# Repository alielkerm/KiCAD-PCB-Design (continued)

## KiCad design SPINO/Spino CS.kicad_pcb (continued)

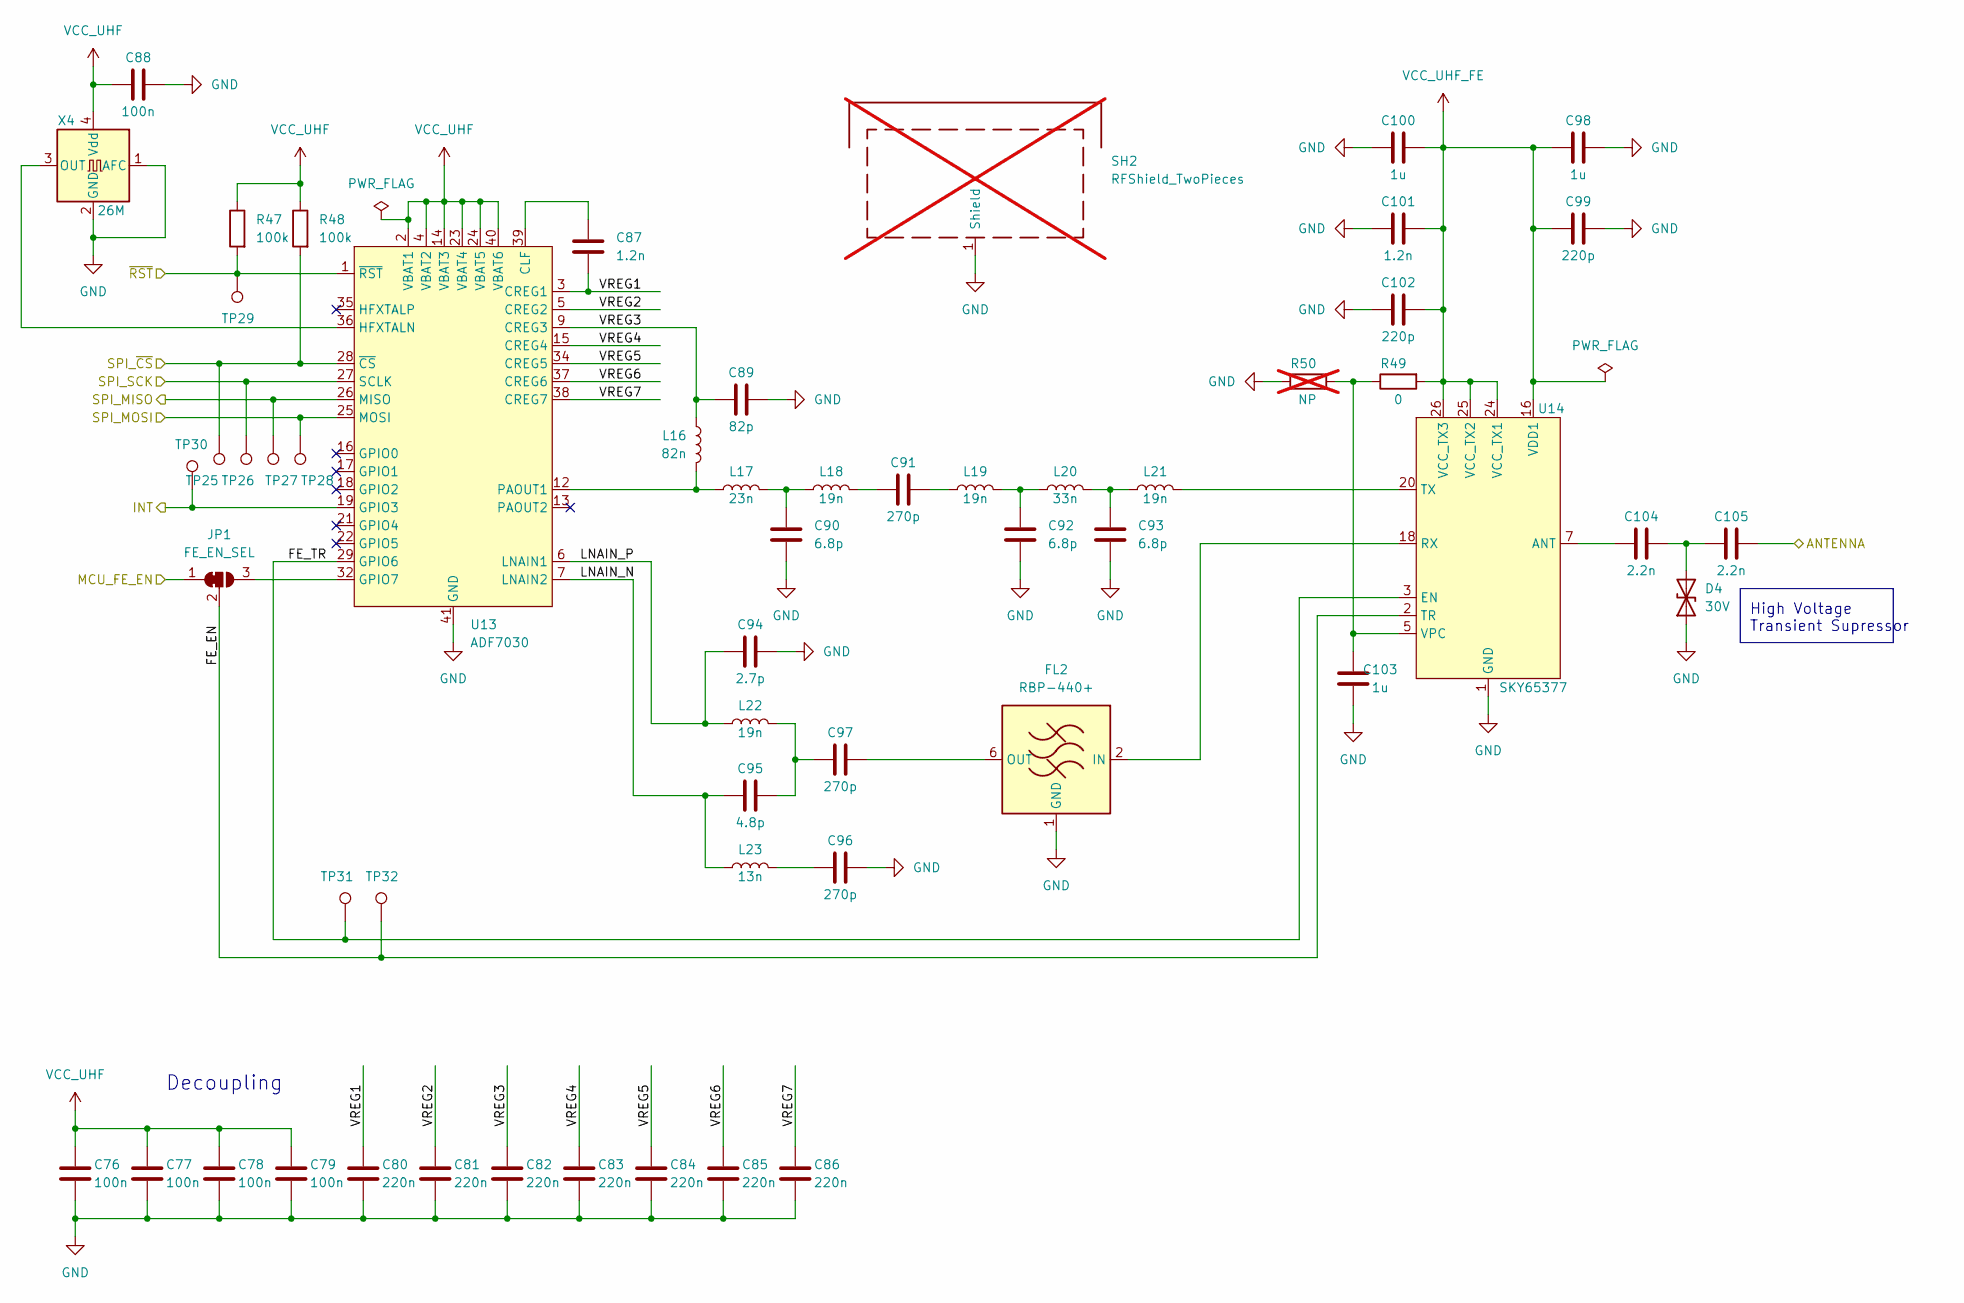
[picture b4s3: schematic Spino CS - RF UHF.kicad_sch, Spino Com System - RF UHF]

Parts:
C76, C77, C78, C79, C88: 100n; C_0402_1005Metric
C80, C81, C82, C83, C84, C85, C86: 220n; C_0402_1005Metric; Tolerance 10%
C87, C101: 1.2n; C_0402_1005Metric; Tolerance 10%
C89: 82p; C_0402_1005Metric; Tolerance 1%
C90, C92, C93: 6.8p; C_0603_1608Metric; Tolerance 0.1p
C91: 270p; C_0603_1608Metric; Tolerance 1%
C94: 2.7p; C_0402_1005Metric; Tolerance 0.05p
C95: 4.8p; C_0402_1005Metric; Tolerance 0.1p
C96, C97: 270p; C_0402_1005Metric; Tolerance 1%
C98, C100, C103: 1u; C_0402_1005Metric
C99, C102: 220p; C_0402_1005Metric; Tolerance 1%
C104, C105: 2.2n; C_0402_1005Metric; Tolerance 10%
D4: 30V; D_0603_1608Metric
FL2: RBP-440+; Mini-Circuits_GP731
JP1: FE_EN_SEL; SolderJumper-3_P0.8mm_Bridged2Bar12_RoundedPad0.6x1.0mm
L16: 82n; L_0603_1608Metric; Tolerance 5%
L17: 23n; L_0402_1005Metric; Tolerance 2%
L18, L19, L21, L22: 19n; L_0402_1005Metric; Tolerance 2%
L20: 33n; L_0402_1005Metric; Tolerance 2%
L23: 13n; L_0402_1005Metric; Tolerance 2%
R47, R48: 100k; R_0402_1005Metric; Tolerance 1%
R49: 0; R_0402_1005Metric
R50: NP; R_0402_1005Metric; not fitted
SH2: RFShield_TwoPieces; Wuerth_3670405_40.5x18.9mm_CustomBottomRightOpening2.2mm; not fitted
TP25: UHF_~{CS}; TestPoint_Pad_D1.0mm
TP26: UHF_SCK; TestPoint_Pad_D1.0mm
TP27: UHF_MISO; TestPoint_Pad_D1.0mm
TP28: UHF_MOSI; TestPoint_Pad_D1.0mm
TP29: UHF_~{RST}; TestPoint_Pad_D1.0mm
TP30: UHF_INT; TestPoint_Pad_D1.0mm
TP31: UHF_FE_TR; TestPoint_Pad_D1.0mm
TP32: UHF_FE_EN; TestPoint_Pad_D1.0mm
U13: ADF7030; LFCSP-40-1EP_6x6mm_P0.5mm_EP4.6x4.6mm
U14: SKY65377; Skyworks_MCM-L-28-1EP_6x6mm_P0.75mm_EP4x4mm
X4: 26M; Oscillator_SMD_TXC_7Z-4Pin_2.0x1.6mm

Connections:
/Processor/UHF_FE_EN: JP1.1 (A); also elsewhere on the board
/Processor/UHF_INT: TP30.1, U13.19 (GPIO3); also elsewhere on the board
/Processor/UHF_SPI_MISO: TP27.1, U13.26 (MISO); also elsewhere on the board
/Processor/UHF_SPI_MOSI: TP28.1, U13.25 (MOSI); also elsewhere on the board
/Processor/UHF_SPI_SCK: TP26.1, U13.27 (SCLK); also elsewhere on the board
/Processor/UHF_SPI_~CS: R48.2, TP25.1, U13.28 (~CS); also elsewhere on the board
/Processor/UHF_~RST: R47.2, TP29.1, U13.1 (~RST); also elsewhere on the board
/RF UHF/ANTENNA: C105.2; also elsewhere on the board
/RF UHF/FE_EN: JP1.2 (C), TP32.1, U14.2 (TR)
/RF UHF/FE_TR: TP31.1, U13.29 (GPIO6), U14.3 (EN)
/RF UHF/LNAIN_N: C95.1, L23.1, U13.7 (LNAIN2)
/RF UHF/LNAIN_P: C94.1, L22.1, U13.6 (LNAIN1)
/RF UHF/VREG1: C80.1, C87.2, U13.3 (CREG1)
/RF UHF/VREG2: C81.1, U13.5 (CREG2)
/RF UHF/VREG3: C82.1, C89.1, L16.1, U13.9 (CREG3)
/RF UHF/VREG4: C83.1, U13.15 (CREG4)
/RF UHF/VREG5: C84.1, U13.34 (CREG5)
/RF UHF/VREG6: C85.1, U13.37 (CREG6)
/RF UHF/VREG7: C86.1, U13.38 (CREG7)
GND: C76.2, C77.2, C78.2, C79.2, C80.2, C81.2, C82.2, C83.2, C84.2, C85.2, C86.2, C88.2, C89.2, C90.2, C92.2, C93.2, C94.2, C96.2, C98.1, C99.1, C100.1, C101.1, C102.1, C103.2, D4.1 (A1), FL2.1 (GND), FL2.3 (GND), FL2.4 (GND), FL2.5 (GND), FL2.7 (GND), FL2.8 (GND), R50.1, SH2.1 (Shield), U13.41 (GND), U14.1 (GND), U14.6 (GND), U14.8 (GND), U14.9 (GND), U14.11 (GND), U14.12 (GND), U14.15 (GND), U14.19 (GND), U14.21 (GND), U14.22 (GND), U14.27 (GND), U14.28 (GND), U14.29 (GND), X4.1 (AFC), X4.2 (GND); also elsewhere on the board
unnamed: C90.1, L17.2, L18.1
unnamed: C91.1, L18.2
unnamed: C91.2, L19.1
unnamed: C92.1, L19.2, L20.1
unnamed: C93.1, L20.2, L21.1
unnamed: C95.2, C97.1, L22.2
unnamed: C96.1, L23.2
unnamed: C104.2, C105.1, D4.2 (A2)
unnamed: FL2.2 (IN), U14.18 (RX)
unnamed: C97.2, FL2.6 (OUT)
unnamed: JP1.3 (B), U13.32 (GPIO7)
unnamed: C87.1, U13.39 (CLF)
unnamed: U13.36 (HFXTALN), X4.3 (OUT)
unnamed: L16.2, L17.1, U13.12 (PAOUT1)
unnamed: C104.1, U14.7 (ANT)
unnamed: L21.2, U14.20 (TX)
unnamed: C103.1, R49.1, R50.2, U14.5 (VPC)
VCC_UHF: C76.1, C77.1, C78.1, C79.1, C88.1, R47.1, R48.1, U13.2 (VBAT1), U13.4 (VBAT2), U13.14 (VBAT3), U13.23 (VBAT4), U13.24 (VBAT5), U13.40 (VBAT6), X4.4 (Vdd); also elsewhere on the board
VCC_UHF_FE: C98.2, C99.2, C100.2, C101.2, C102.2, R49.2, U14.16 (VDD1), U14.24 (VCC_TX1), U14.25 (VCC_TX2), U14.26 (VCC_TX3); also elsewhere on the board

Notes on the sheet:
High Voltage Transient Supressor
Decoupling

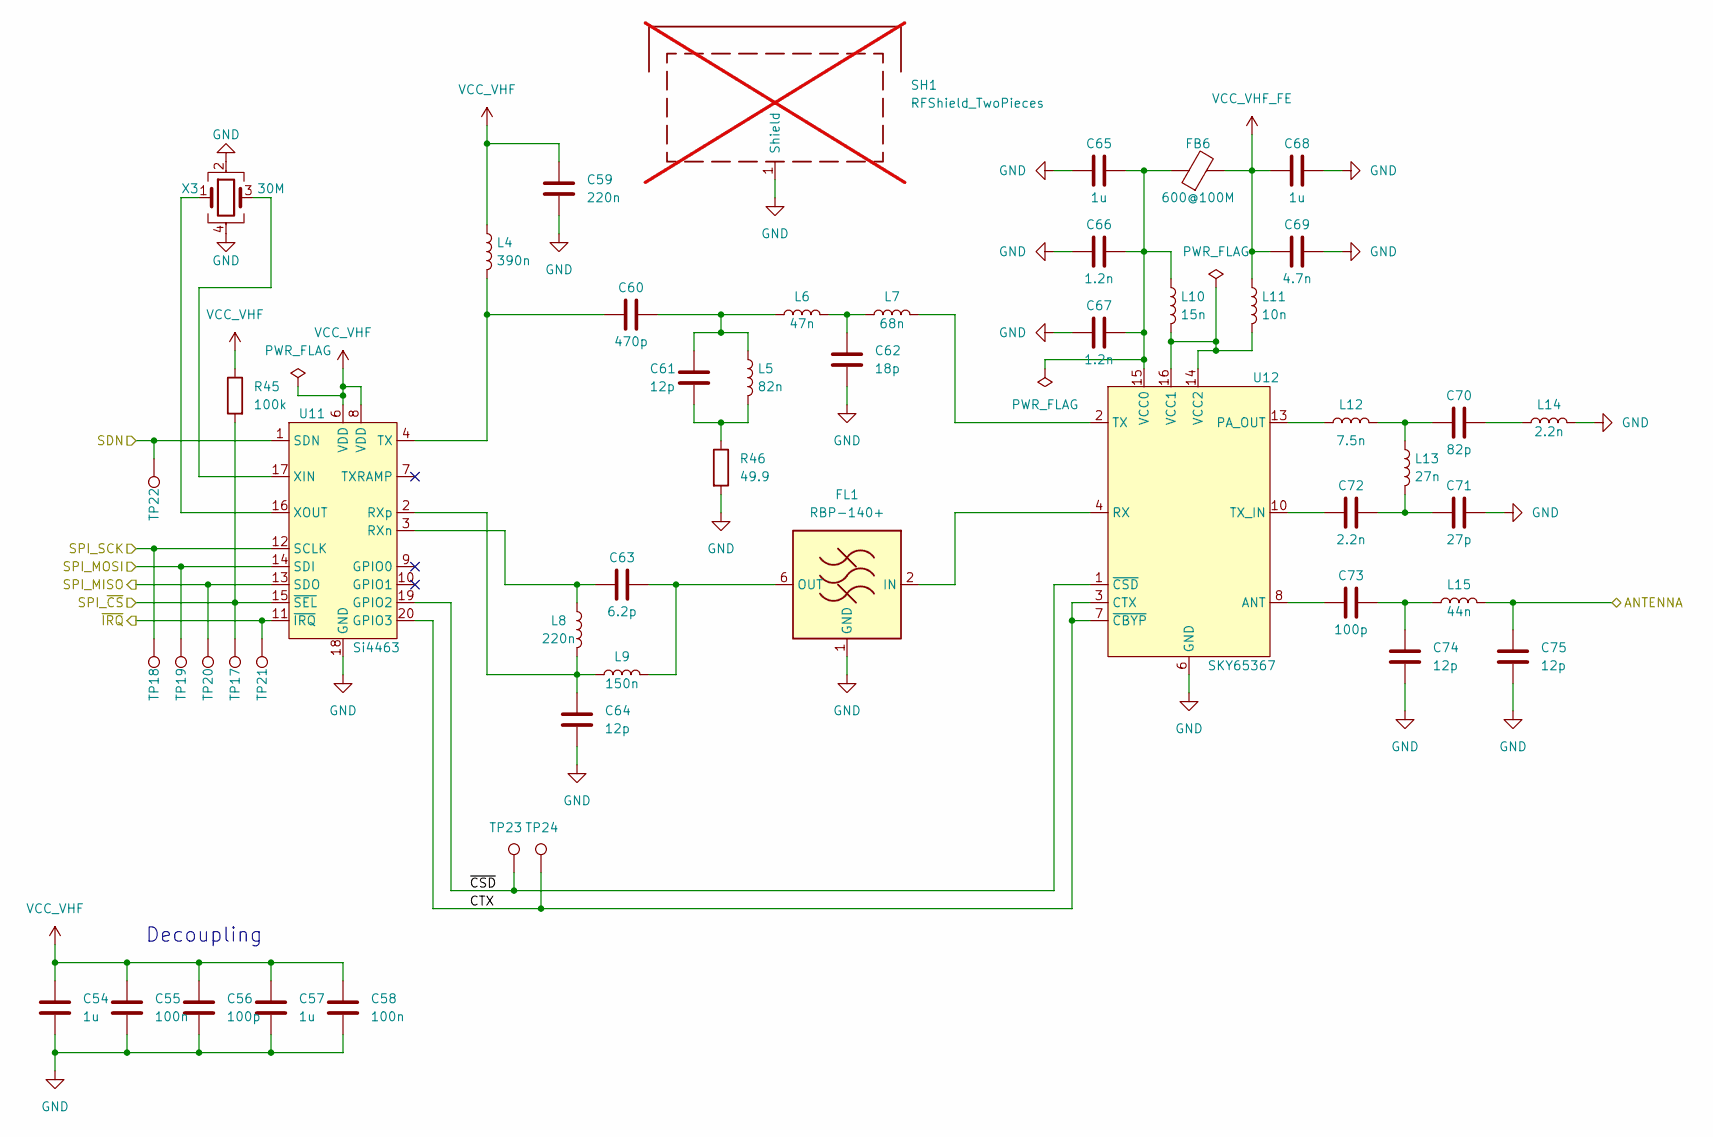
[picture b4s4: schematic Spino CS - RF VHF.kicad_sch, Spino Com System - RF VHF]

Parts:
C54, C57, C65, C68: 1u; C_0402_1005Metric
C55, C58: 100n; C_0402_1005Metric
C56, C73: 100p; C_0402_1005Metric; Tolerance 1%
C59: 220n; C_0402_1005Metric; Tolerance 10%
C60: 470p; C_0402_1005Metric; Tolerance 1%
C61, C64, C74, C75: 12p; C_0603_1608Metric; Tolerance 1%
C62: 18p; C_0603_1608Metric; Tolerance 1%
C63: 6.2p; C_0603_1608Metric; Tolerance 0.1p
C66, C67: 1.2n; C_0402_1005Metric; Tolerance 10%
C69: 4.7n; C_0402_1005Metric; Tolerance 10%
C70: 82p; C_0402_1005Metric; Tolerance 1%
C71: 27p; C_0603_1608Metric; Tolerance 1%
C72: 2.2n; C_0402_1005Metric; Tolerance 10%
FB6: 600@100M; L_0603_1608Metric
FL1: RBP-140+; Mini-Circuits_GP731
L4: 390n; L_0603_1608Metric; Tolerance 5%
L5: 82n; L_0603_1608Metric; Tolerance 5%
L6: 47n; L_0402_1005Metric; Tolerance 2%
L7: 68n; L_0402_1005Metric; Tolerance 2%
L8: 220n; L_0603_1608Metric; Tolerance 5%
L9: 150n; L_0603_1608Metric; Tolerance 5%
L10: 15n; L_0402_1005Metric; Tolerance 5%
L11: 10n; L_0603_1608Metric; Tolerance 5%
L12: 7.5n; L_0603_1608Metric; Tolerance 2%
L13: 27n; L_0603_1608Metric; Tolerance 2%
L14: 2.2n; L_0402_1005Metric; Tolerance 2%
L15: 44n; L_0603_1608Metric; Tolerance 2%
R45: 100k; R_0402_1005Metric; Tolerance 1%
R46: 49.9; R_0603_1608Metric; Tolerance 1%
SH1: RFShield_TwoPieces; Wuerth_3670405_40.5x18.9mm_CustomBottomLeftOpening2.2mm; not fitted
TP17: VHF_~{CS}; TestPoint_Pad_D1.0mm
TP18: VHF_CLK; TestPoint_Pad_D1.0mm
TP19: VHF_MOSI; TestPoint_Pad_D1.0mm
TP20: VHF_MISO; TestPoint_Pad_D1.0mm
TP21: VHF_~{IRQ}; TestPoint_Pad_D1.0mm
TP22: VHF_SDN; TestPoint_Pad_D1.0mm
TP23: VHF_FE_~{CSD}; TestPoint_Pad_D1.0mm
TP24: VHF_FE_CTX; TestPoint_Pad_D1.0mm
U11: Si4463; QFN-20-1EP_4x4mm_P0.5mm_EP2.6x2.6mm
U12: SKY65367; Skyworks_MCM-L-16-1EP_4x4mm_P0.8mm_EP2x2mm
X3: 30M; Crystal_SMD_2016-4Pin_2.0x1.6mm

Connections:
/Processor/VHF_SDN: TP22.1, U11.1 (SDN); also elsewhere on the board
/Processor/VHF_SPI_MISO: TP20.1, U11.13 (SDO); also elsewhere on the board
/Processor/VHF_SPI_MOSI: TP19.1, U11.14 (SDI); also elsewhere on the board
/Processor/VHF_SPI_SCK: TP18.1, U11.12 (SCLK); also elsewhere on the board
/Processor/VHF_SPI_~CS: R45.2, TP17.1, U11.15 (~SEL); also elsewhere on the board
/Processor/VHF_~IRQ: TP21.1, U11.11 (~IRQ); also elsewhere on the board
/RF VHF/ANTENNA: C75.1, L15.2; also elsewhere on the board
/RF VHF/CTX: TP24.1, U11.20 (GPIO3), U12.3 (CTX), U12.7 (~CBYP)
/RF VHF/~CSD: TP23.1, U11.19 (GPIO2), U12.1 (~CSD)
GND: C54.2, C55.2, C56.2, C57.2, C58.2, C59.2, C62.2, C64.2, C65.2, C66.2, C67.2, C68.2, C69.2, C71.2, C74.2, C75.2, FL1.1 (GND), FL1.3 (GND), FL1.4 (GND), FL1.5 (GND), FL1.7 (GND), FL1.8 (GND), L14.2, R46.2, SH1.1 (Shield), U11.18 (GND), U11.21 (GND), U12.6 (GND), U12.9 (GND), U12.11 (GND), U12.12 (GND), U12.17 (GND), X3.2, X3.4; also elsewhere on the board
unnamed: C60.2, C61.1, L5.1, L6.1
unnamed: C61.2, L5.2, R46.1
unnamed: C62.1, L6.2, L7.1
unnamed: C70.1, L12.2, L13.1
unnamed: C70.2, L14.1
unnamed: C71.1, C72.2, L13.2
unnamed: C73.2, C74.1, L15.1
unnamed: FL1.2 (IN), U12.4 (RX)
unnamed: C63.2, FL1.6 (OUT), L9.2
unnamed: C63.1, L8.1, U11.3 (RXn)
unnamed: C64.1, L8.2, L9.1, U11.2 (RXp)
unnamed: C60.1, L4.2, U11.4 (TX)
unnamed: U11.17 (XIN), X3.3
unnamed: U11.16 (XOUT), X3.1
unnamed: C73.1, U12.8 (ANT)
unnamed: L12.1, U12.13 (PA_OUT)
unnamed: L7.2, U12.2 (TX)
unnamed: C72.1, U12.10 (TX_IN)
unnamed: C65.1, C66.1, C67.1, FB6.1, L10.1, U12.15 (VCC0)
VCC_VHF: C54.1, C55.1, C56.1, C57.1, C58.1, C59.1, L4.1, R45.1, U11.6 (VDD), U11.8 (VDD); also elsewhere on the board
VCC_VHF_FE: C68.1, C69.1, FB6.2, L11.1; also elsewhere on the board

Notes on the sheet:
Decoupling

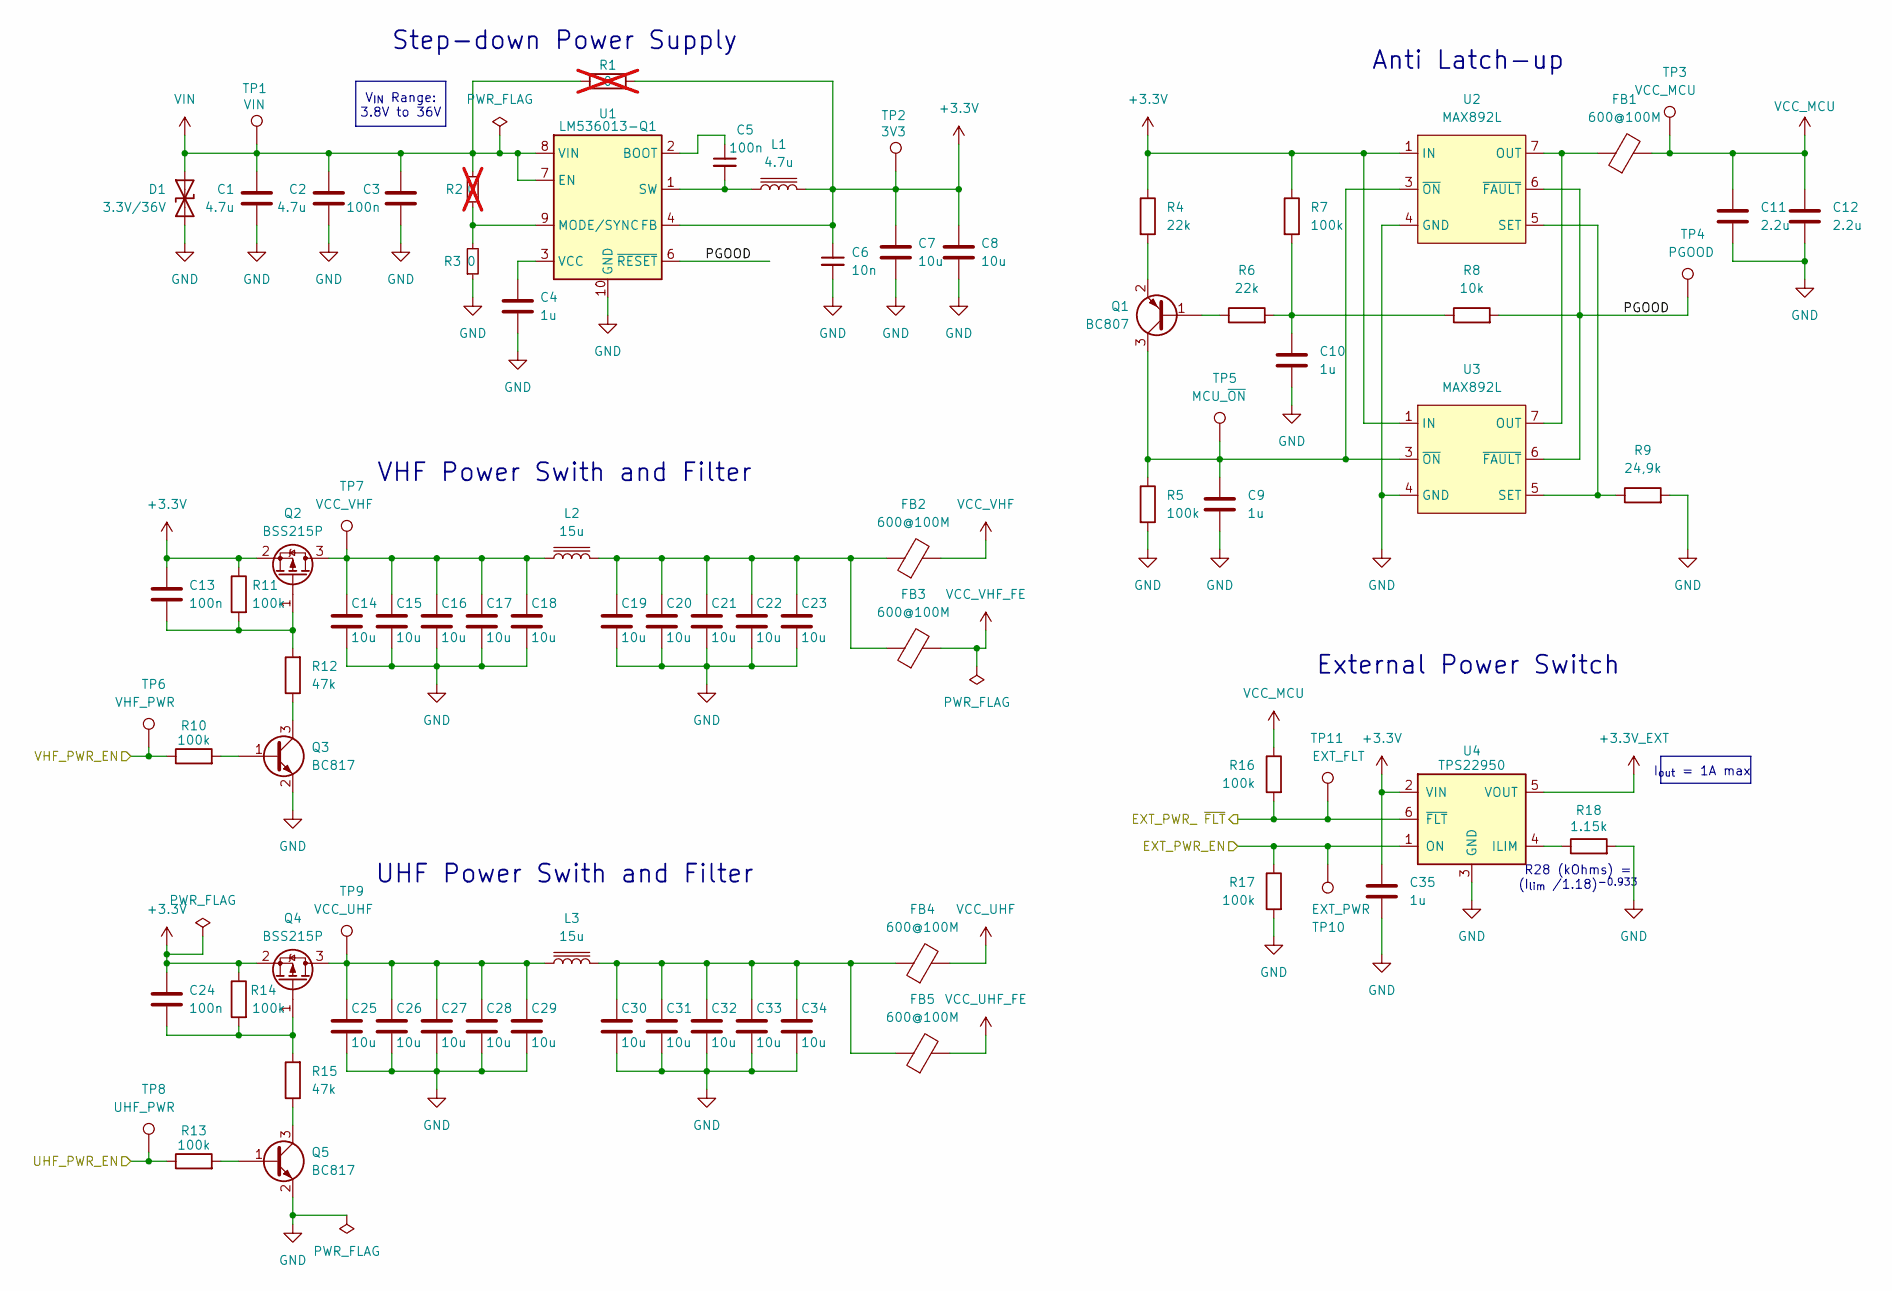
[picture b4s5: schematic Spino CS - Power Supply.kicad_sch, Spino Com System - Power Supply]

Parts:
C1, C2: 4.7u; C_0805_2012Metric; Tolerance 10%
C3: 100n; C_0603_1608Metric
C4: 1u; C_0402_1005Metric
C5, C13, C24: 100n; C_0402_1005Metric
C6: 10n; C_0402_1005Metric
C7, C8, C14, C15, C16, C17, C18, C19, C20, C21, C22, C23, C25, C26, C27, C28, C29, C30, C31, C32, C33, C34: 10u; C_0805_2012Metric; Tolerance 10%
C9, C10, C35: 1u; C_0603_1608Metric; Tolerance 10%
C11, C12: 2.2u; C_0603_1608Metric; Tolerance 10%
D1: 3.3V/36V; D_SOD-123F
FB1, FB2, FB3, FB4, FB5: 600@100M; L_0603_1608Metric
L1: 4.7u; L_Coilcraft_XxL4040
L2, L3: 15u; L_TDK_CLF7045
Q1: BC807; SOT-23
Q2, Q4: BSS215P; SOT-23-3
Q3, Q5: BC817; SOT-23-3
R1: 0; R_0805_2012Metric; not fitted
R2: 0; R_0402_1005Metric; not fitted
R3: 0; R_0402_1005Metric
R4, R6: 22k; R_0402_1005Metric; Tolerance 1%
R5, R7, R10, R11, R13, R14, R16, R17: 100k; R_0402_1005Metric; Tolerance 1%
R8: 10k; R_0402_1005Metric; Tolerance 1%
R9: 24,9k; R_0402_1005Metric; Tolerance 1%
R12, R15: 47k; R_0402_1005Metric; Tolerance 1%
R18: 1.15k; R_0402_1005Metric; Tolerance 1%
TP1: VIN; TestPoint_Pad_D1.0mm
TP2: 3V3; TestPoint_Pad_D1.0mm
TP3: VCC_MCU; TestPoint_Pad_D1.0mm
TP4: PGOOD; TestPoint_Pad_D1.0mm
TP5: MCU_~{ON}; TestPoint_Pad_D1.0mm
TP6: VHF_PWR; TestPoint_Pad_D1.0mm
TP7: VCC_VHF; TestPoint_Pad_D1.0mm
TP8: UHF_PWR; TestPoint_Pad_D1.0mm
TP9: VCC_UHF; TestPoint_Pad_D1.0mm
TP10: EXT_PWR; TestPoint_Pad_D1.0mm
TP11: EXT_FLT; TestPoint_Pad_D1.0mm
U1: LM536013-Q1; Texas_S-PVSON-N10
U2, U3: MAX892L; MSOP-8_3x3mm_P0.65mm
U4: TPS22950; SOT-23-6

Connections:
+3.3V: C6.1, C7.1, C8.1, C13.1, C24.1, C35.1, L1.2, Q2.2 (S), Q4.2 (S), R1.2, R4.1, R7.1, R11.1, R14.1, TP2.1, U1.4 (FB), U2.1 (IN), U2.2 (IN), U3.1 (IN), U3.2 (IN), U4.2 (VIN)
+3.3V_EXT: U4.5 (VOUT); also elsewhere on the board
/Power Supply/EXT_PWR_ ~FLT: R16.2, TP11.1, U4.6 (~FLT); also elsewhere on the board
/Power Supply/EXT_PWR_EN: R17.1, TP10.1, U4.1 (ON); also elsewhere on the board
/Power Supply/PGOOD: R8.2, TP4.1, U1.6 (~RESET), U2.6 (~FAULT), U3.6 (~FAULT)
/Power Supply/UHF_PWR_EN: R13.1, TP8.1; also elsewhere on the board
/Power Supply/VHF_PWR_EN: R10.1, TP6.1; also elsewhere on the board
GND: C1.2, C2.2, C3.2, C4.2, C6.2, C7.2, C8.2, C9.2, C10.2, C11.2, C12.2, C14.2, C15.2, C16.2, C17.2, C18.2, C19.2, C20.2, C21.2, C22.2, C23.2, C25.2, C26.2, C27.2, C28.2, C29.2, C30.2, C31.2, C32.2, C33.2, C34.2, C35.2, D1.2 (A2), Q3.2 (E), Q5.2 (E), R3.1, R5.2, R9.2, R17.2, R18.2, U1.5 (AGND), U1.10 (GND), U1.11 (PAD), U2.4 (GND), U3.4 (GND), U4.3 (GND); also elsewhere on the board
unnamed: C10.1, R6.2, R7.2, R8.1
unnamed: C19.1, C20.1, C21.1, C22.1, C23.1, FB2.1, FB3.1, L2.2
unnamed: C30.1, C31.1, C32.1, C33.1, C34.1, FB4.1, FB5.1, L3.2
unnamed: FB1.1, U2.7 (OUT), U2.8 (OUT), U3.7 (OUT), U3.8 (OUT)
unnamed: Q1.1 (B), R6.1
unnamed: C9.1, Q1.3 (C), R5.1, TP5.1, U2.3 (~ON), U3.3 (~ON)
unnamed: Q1.2 (E), R4.2
unnamed: C14.1, C15.1, C16.1, C17.1, C18.1, L2.1, Q2.3 (D), TP7.1
unnamed: C13.2, Q2.1 (G), R11.2, R12.2
unnamed: Q3.1 (B), R10.2
unnamed: Q3.3 (C), R12.1
unnamed: C25.1, C26.1, C27.1, C28.1, C29.1, L3.1, Q4.3 (D), TP9.1
unnamed: C24.2, Q4.1 (G), R14.2, R15.2
unnamed: Q5.1 (B), R13.2
unnamed: Q5.3 (C), R15.1
unnamed: C5.1, U1.2 (BOOT)
unnamed: R2.1, R3.2, U1.9 (MODE/SYNC)
unnamed: C5.2, L1.1, U1.1 (SW)
unnamed: C4.1, U1.3 (VCC)
unnamed: R9.1, U2.5 (SET), U3.5 (SET)
unnamed: R18.1, U4.4 (ILIM)
VCC_MCU: C11.1, C12.1, FB1.2, R16.1, TP3.1; also elsewhere on the board
VCC_UHF: FB4.2; also elsewhere on the board
VCC_UHF_FE: FB5.2; also elsewhere on the board
VCC_VHF: FB2.2; also elsewhere on the board
VCC_VHF_FE: FB3.2; also elsewhere on the board
VIN: C1.1, C2.1, C3.1, D1.1 (A1), R1.1, R2.2, TP1.1, U1.7 (EN), U1.8 (VIN); also elsewhere on the board

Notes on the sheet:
I_{out} = 1A max
V_{IN} Range: 3.8V to 36V
R28 (kOhms) = (I_{lim} /1.18)^{-0.933}
External Power Switch
Anti Latch-up
Step-down Power Supply
VHF Power Swith and Filter
UHF Power Swith and Filter

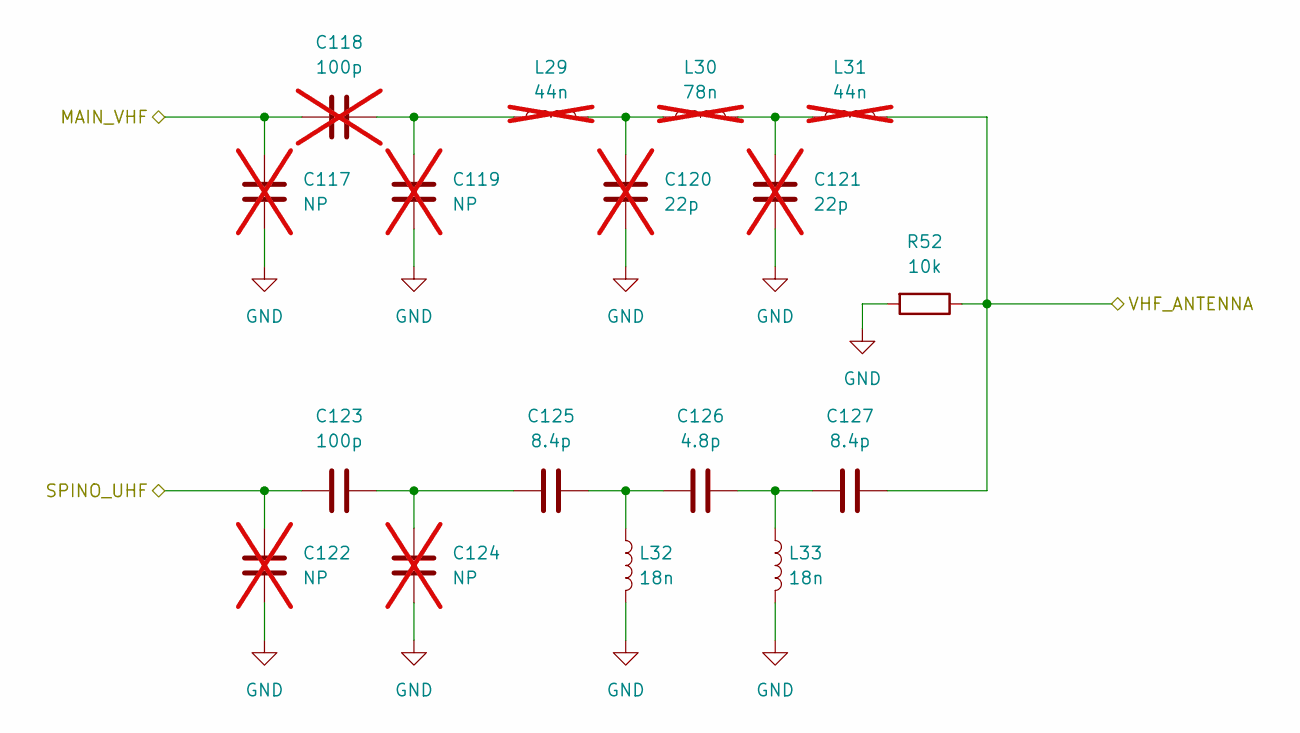
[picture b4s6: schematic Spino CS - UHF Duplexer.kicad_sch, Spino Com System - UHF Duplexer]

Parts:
C117, C119, C122, C124: NP; C_0603_1608Metric; not fitted
C118: 100p; C_0402_1005Metric; Tolerance 1%; not fitted
C120, C121: 22p; C_0603_1608Metric; Tolerance 1%; not fitted
C123: 100p; C_0402_1005Metric; Tolerance 1%
C125, C127: 8.4p; C_0402_1005Metric; Tolerance 0.1p
C126: 4.8p; C_0402_1005Metric; Tolerance 0.1p
L29, L31: 44n; L_0603_1608Metric; Tolerance 2%; not fitted
L30: 78n; L_0603_1608Metric; Tolerance 2%; not fitted
L32, L33: 18n; L_0603_1608Metric; Tolerance 2%
R52: 10k; R_0603_1608Metric; Tolerance 1%

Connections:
/RF UHF/ANTENNA: C122.1, C123.1; also elsewhere on the board
/UHF Duplexer/MAIN_VHF: C117.1, C118.1; also elsewhere on the board
/UHF Duplexer/VHF_ANTENNA: C127.2, L31.2, R52.1; also elsewhere on the board
GND: C117.2, C119.2, C120.2, C121.2, C122.2, C124.2, L32.2, L33.2, R52.2; also elsewhere on the board
unnamed: C118.2, C119.1, L29.1
unnamed: C120.1, L29.2, L30.1
unnamed: C121.1, L30.2, L31.1
unnamed: C123.2, C124.1, C125.1
unnamed: C125.2, C126.1, L32.1
unnamed: C126.2, C127.1, L33.1

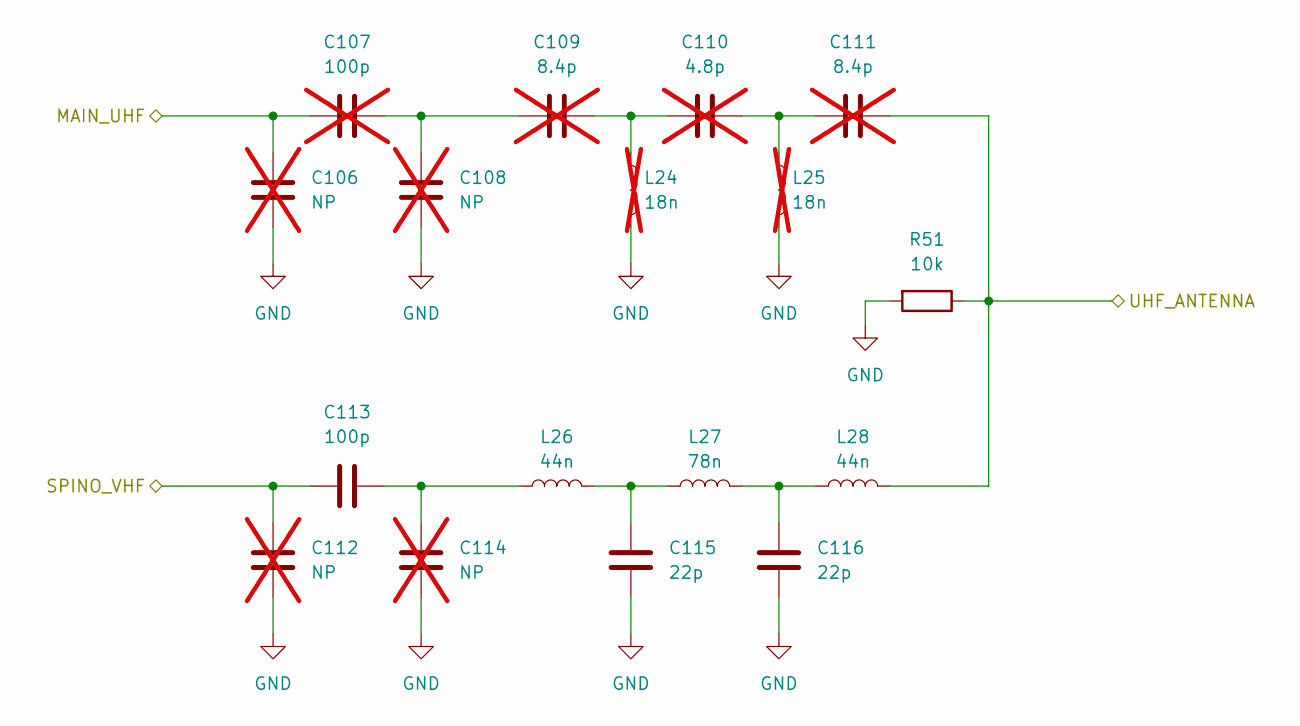
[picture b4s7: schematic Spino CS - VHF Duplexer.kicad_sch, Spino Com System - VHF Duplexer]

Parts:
C106, C108, C112, C114: NP; C_0603_1608Metric; not fitted
C107: 100p; C_0402_1005Metric; Tolerance 1%; not fitted
C109, C111: 8.4p; C_0402_1005Metric; Tolerance 0.1p; not fitted
C110: 4.8p; C_0402_1005Metric; Tolerance 0.1p; not fitted
C113: 100p; C_0402_1005Metric; Tolerance 1%
C115, C116: 22p; C_0603_1608Metric; Tolerance 1%
L24, L25: 18n; L_0603_1608Metric; Tolerance 2%; not fitted
L26, L28: 44n; L_0603_1608Metric; Tolerance 2%
L27: 78n; L_0603_1608Metric; Tolerance 2%
R51: 10k; R_0603_1608Metric; Tolerance 1%

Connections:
/RF VHF/ANTENNA: C112.1, C113.1; also elsewhere on the board
/VHF Duplexer/MAIN_UHF: C106.1, C107.1; also elsewhere on the board
/VHF Duplexer/UHF_ANTENNA: C111.2, L28.2, R51.1; also elsewhere on the board
GND: C106.2, C108.2, C112.2, C114.2, C115.2, C116.2, L24.2, L25.2, R51.2; also elsewhere on the board
unnamed: C107.2, C108.1, C109.1
unnamed: C109.2, C110.1, L24.1
unnamed: C110.2, C111.1, L25.1
unnamed: C113.2, C114.1, L26.1
unnamed: C115.1, L26.2, L27.1
unnamed: C116.1, L27.2, L28.1

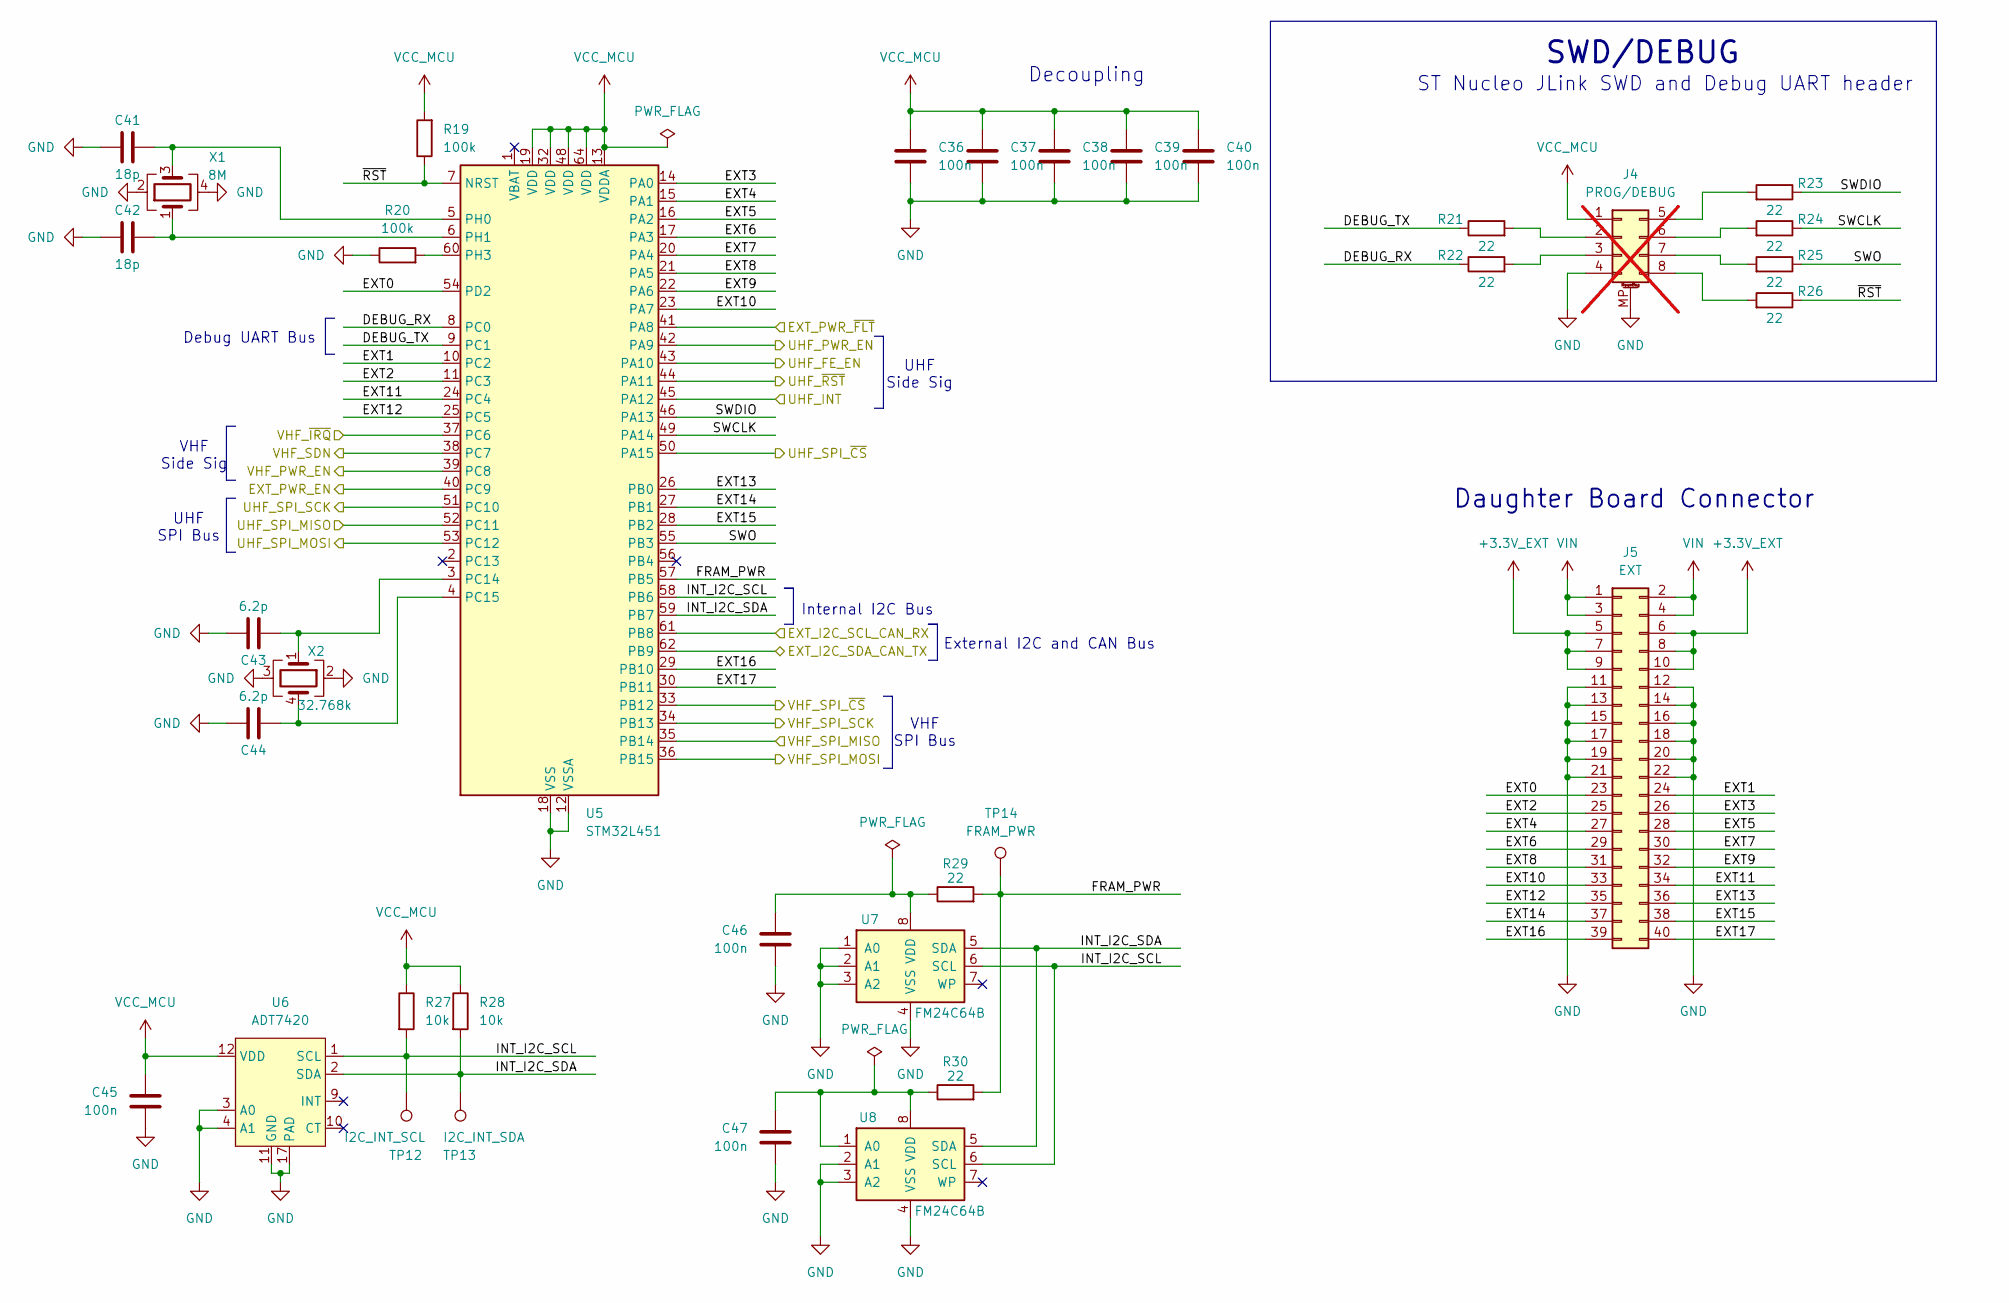
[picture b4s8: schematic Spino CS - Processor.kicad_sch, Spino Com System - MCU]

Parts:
C36, C37, C38, C39, C40, C45, C46, C47: 100n; C_0402_1005Metric
C41, C42: 18p; C_0402_1005Metric; Tolerance 1%
C43, C44: 6.2p; C_0402_1005Metric; Tolerance 0.1p
J4: PROG/DEBUG; Harwin_LTek-Male_2x04_P2.00mm_Horizontal_StrainRelief; not fitted
J5: EXT; Samtec_LSEM-120-xx.x-x-DV-A-N_2x20_P0.80mm_Vertical
R19, R20: 100k; R_0402_1005Metric; Tolerance 1%
R21, R22, R23, R24, R25, R26, R29, R30: 22; R_0402_1005Metric; Tolerance 1%
R27, R28: 10k; R_0402_1005Metric; Tolerance 1%
TP12: I2C_INT_SCL; TestPoint_Pad_D1.0mm
TP13: I2C_INT_SDA; TestPoint_Pad_D1.0mm
TP14: FRAM_PWR; TestPoint_Pad_D1.0mm
U5: STM32L451; LQFP-64_10x10mm_P0.5mm
U6: ADT7420; LFCSP-16-1EP_4x4mm_P0.65mm_EP2.6x2.6mm
U7, U8: FM24C64B; SOIC-8_3.9x4.9mm_P1.27mm
X1: 8M; Crystal_SMD_Abracon_ABM8AIG-4Pin_3.2x2.5mm
X2: 32.768k; Crystal_SMD_Abracon_ABS25-4Pin_8.0x3.8mm

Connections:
+3.3V_EXT: J5.5, J5.6, J5.7, J5.8, J5.9, J5.10; also elsewhere on the board
/Digital Serial/EXT_I2C_SCL_CAN_RX: U5.61 (PB8); also elsewhere on the board
/Digital Serial/EXT_I2C_SDA_CAN_TX: U5.62 (PB9); also elsewhere on the board
/Power Supply/EXT_PWR_ ~FLT: U5.41 (PA8); also elsewhere on the board
/Power Supply/EXT_PWR_EN: U5.40 (PC9); also elsewhere on the board
/Power Supply/UHF_PWR_EN: U5.42 (PA9); also elsewhere on the board
/Power Supply/VHF_PWR_EN: U5.39 (PC8); also elsewhere on the board
/Processor/DEBUG_RX: R22.1, U5.8 (PC0)
/Processor/DEBUG_TX: R21.1, U5.9 (PC1)
/Processor/EXT0: J5.23, U5.54 (PD2)
/Processor/EXT1: J5.24, U5.10 (PC2)
/Processor/EXT2: J5.25, U5.11 (PC3)
/Processor/EXT3: J5.26, U5.14 (PA0)
/Processor/EXT4: J5.27, U5.15 (PA1)
/Processor/EXT5: J5.28, U5.16 (PA2)
/Processor/EXT6: J5.29, U5.17 (PA3)
/Processor/EXT7: J5.30, U5.20 (PA4)
/Processor/EXT8: J5.31, U5.21 (PA5)
/Processor/EXT9: J5.32, U5.22 (PA6)
/Processor/EXT10: J5.33, U5.23 (PA7)
/Processor/EXT11: J5.34, U5.24 (PC4)
/Processor/EXT12: J5.35, U5.25 (PC5)
/Processor/EXT13: J5.36, U5.26 (PB0)
/Processor/EXT14: J5.37, U5.27 (PB1)
/Processor/EXT15: J5.38, U5.28 (PB2)
/Processor/EXT16: J5.39, U5.29 (PB10)
/Processor/EXT17: J5.40, U5.30 (PB11)
/Processor/FRAM_PWR: R29.2, R30.2, TP14.1, U5.57 (PB5)
/Processor/INT_I2C_SCL: R27.2, TP12.1, U5.58 (PB6), U6.1 (SCL), U7.6 (SCL), U8.6 (SCL)
/Processor/INT_I2C_SDA: R28.2, TP13.1, U5.59 (PB7), U6.2 (SDA), U7.5 (SDA), U8.5 (SDA)
/Processor/SWCLK: R24.1, U5.49 (PA14)
/Processor/SWDIO: R23.1, U5.46 (PA13)
/Processor/SWO: R25.1, U5.55 (PB3)
/Processor/UHF_FE_EN: U5.43 (PA10); also elsewhere on the board
/Processor/UHF_INT: U5.45 (PA12); also elsewhere on the board
/Processor/UHF_SPI_MISO: U5.52 (PC11); also elsewhere on the board
/Processor/UHF_SPI_MOSI: U5.53 (PC12); also elsewhere on the board
/Processor/UHF_SPI_SCK: U5.51 (PC10); also elsewhere on the board
/Processor/UHF_SPI_~CS: U5.50 (PA15); also elsewhere on the board
/Processor/UHF_~RST: U5.44 (PA11); also elsewhere on the board
/Processor/VHF_SDN: U5.38 (PC7); also elsewhere on the board
/Processor/VHF_SPI_MISO: U5.35 (PB14); also elsewhere on the board
/Processor/VHF_SPI_MOSI: U5.36 (PB15); also elsewhere on the board
/Processor/VHF_SPI_SCK: U5.34 (PB13); also elsewhere on the board
/Processor/VHF_SPI_~CS: U5.33 (PB12); also elsewhere on the board
/Processor/VHF_~IRQ: U5.37 (PC6); also elsewhere on the board
/Processor/~RST: R19.1, R26.1, U5.7 (NRST)
GND: C36.2, C37.2, C38.2, C39.2, C40.2, C41.2, C42.2, C43.2, C44.2, C45.2, C46.2, C47.2, J4.4, J4.MP (MountPin), J5.11, J5.12, J5.13, J5.14, J5.15, J5.16, J5.17, J5.18, J5.19, J5.20, J5.21, J5.22, R20.1, U5.12 (VSSA), U5.18 (VSS), U5.31 (VSS), U5.47 (VSS), U5.63 (VSS), U6.3 (A0), U6.4 (A1), U6.11 (GND), U6.17 (PAD), U7.1 (A0), U7.2 (A1), U7.3 (A2), U7.4 (VSS), U8.2 (A1), U8.3 (A2), U8.4 (VSS), X1.2, X1.4, X2.2, X2.3; also elsewhere on the board
unnamed: J4.2, R21.2
unnamed: J4.3, R22.2
unnamed: J4.5, R23.2
unnamed: J4.6, R24.2
unnamed: J4.7, R25.2
unnamed: J4.8, R26.2
unnamed: C43.1, U5.3 (PC14), X2.1
unnamed: C44.1, U5.4 (PC15), X2.4
unnamed: C41.1, U5.5 (PH0), X1.3
unnamed: C42.1, U5.6 (PH1), X1.1
unnamed: R20.2, U5.60 (PH3)
unnamed: C46.1, R29.1, U7.8 (VDD)
unnamed: C47.1, R30.1, U8.1 (A0), U8.8 (VDD)
VCC_MCU: C36.1, C37.1, C38.1, C39.1, C40.1, C45.1, J4.1, R19.2, R27.1, R28.1, U5.13 (VDDA), U5.19 (VDD), U5.32 (VDD), U5.48 (VDD), U5.64 (VDD), U6.12 (VDD); also elsewhere on the board
VIN: J5.1, J5.2, J5.3, J5.4; also elsewhere on the board

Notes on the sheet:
UHF SPI Bus
VHF SPI Bus
External I2C and CAN Bus
Decoupling
Internal I2C Bus
UHF Side Sig
Daughter Board Connector
VHF Side Sig
SWD/DEBUG
Debug UART Bus
ST Nucleo JLink SWD and Debug UART header

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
